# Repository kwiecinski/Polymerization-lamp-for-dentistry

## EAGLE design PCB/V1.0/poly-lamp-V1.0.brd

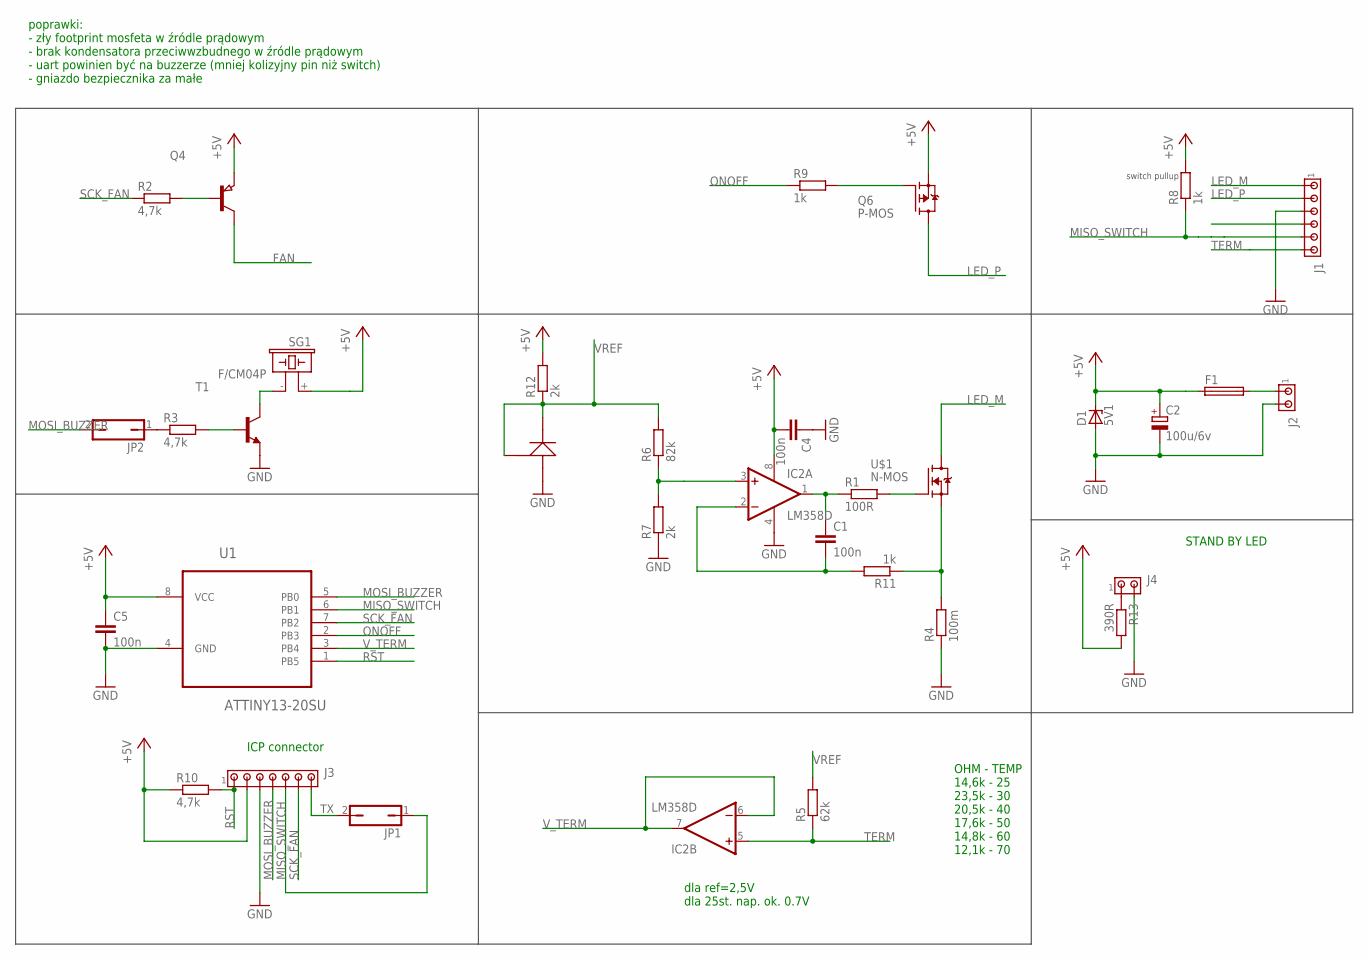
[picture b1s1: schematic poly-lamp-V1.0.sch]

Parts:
C1, C4, C5: 100n; C0805
C2: 100u/6v; E2,5-7
D1: 5V1; DO35Z10
F1: SH22,5
IC2: LM358D; SO08
J1: MTA06-100; 10X06MTA
J2, J4: MTA02-100; 10X02MTA
J3: MTA07-100; 10X07MTA
JP1, JP2: JP1Q; JP1
Q4: PNP-TRANSISTOR_SOT23; SOT23
Q6: P-MOS; TO252
R1: 100R; R0805
R2, R3, R10: 4,7k; R0805
R4: 100m; R0805
R5: 62k; R0805
R6: 82k; R0805
R7, R12: 2k; R0805
R8, R9, R11: 1k; R0805
R13: 390R; R0805
SG1: F/CM04P
T1: BC817-16-NPN-SOT23-BEC; SOT23-BEC
U1: ATTINY13-20SU; SOIC127P798X216-8N
U$1: N-MOS; TO252
U$2: TL431; SOT23-BEC

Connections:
+5V: C2.+, C4.2, C5.1, D1.C, F1.1, IC2.8 (V+), J3.2, Q4.2 (E), Q6.2 (S), R8.2, R10.1, R12.2, R13.2, SG1.+ (1), U1.8 (VCC)
FAN: J1.4, Q4.3 (C)
GND: C2.-, C4.1, C5.2, D1.A, IC2.4 (V-), J1.3, J2.2, J3.3, J4.2, R4.1, R7.1, T1.E, U1.4 (GND), U$2.C (A)
LED_M: J1.1, U$1.3 (D)
LED_P: J1.2, Q6.3 (D)
MISO_SWITCH: J1.5, J3.5, JP1.1, R8.1, U1.6 (PB1)
MOSI_BUZZER: J3.4, JP2.2, U1.5 (PB0)
unnamed: C1.1, IC2.1 (OUT), R1.1
unnamed: R1.2, U$1.1 (G)
unnamed: R3.2, T1.B
unnamed: SG1.- (2), T1.C
unnamed: Q4.1 (B), R2.2
unnamed: IC2.3 (+IN), R6.1, R7.2
unnamed: C1.2, IC2.2 (-IN), R11.2
unnamed: Q6.1 (G), R9.2
unnamed: F1.2, J2.1
unnamed: JP2.1, R3.1
unnamed: J4.1, R13.1
unnamed: R4.2, R11.1, U$1.2 (S)
ONOFF: R9.1, U1.2 (PB3)
RST: J3.1, R10.2, U1.1 (PB5)
SCK_FAN: J3.6, R2.1, U1.7 (PB2)
TERM: IC2.5 (+IN), J1.6, R5.1
TX: J3.7, JP1.2
VREF: R5.2, R6.2, R12.1, U$2.B (K), U$2.E (R)
V_TERM: IC2.6 (-IN), IC2.7 (OUT), U1.3 (PB4)

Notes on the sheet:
OHM - TEMP 14,6k - 25 23,5k - 30 20,5k - 40 17,6k - 50 14,8k - 60 12,1k - 70
dla ref=2,5V dla 25st. nap. ok. 0.7V
ICP connector
switch pullup
poprawki: - zły footprint mosfeta w źródle prądowym - brak kondensatora przeciwwzbudnego w źródle prądowym - uart powinien być na buzzerze (mniej kolizyjny pin niż switch) - gniazdo bezpiecznika za małe
STAND BY LED

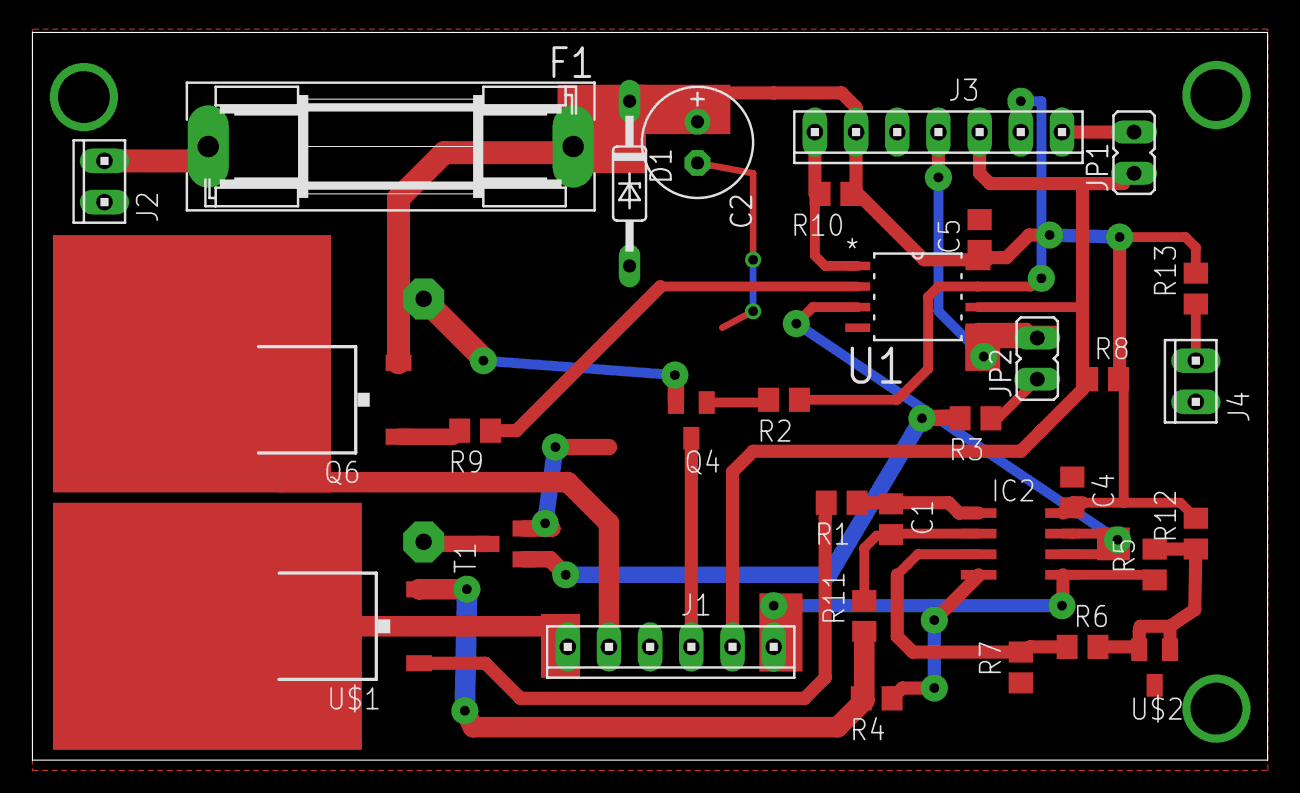
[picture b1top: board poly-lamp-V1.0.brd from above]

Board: 2 copper layers, 76.2 x 44.9 mm, 33 parts (1 on the bottom side), 26 nets.

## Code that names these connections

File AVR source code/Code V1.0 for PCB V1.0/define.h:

/*
 * define.h
 *
 *  Created on: 25 lis 2018
 *      Author: senio
 */
#define 	F_CPU   9600000UL

#define LED (1<<PB3)
#define led_off PORTB |= LED
#define led_on PORTB &= ~LED

#define BUZZ (1<<PB0)
#define buzz_on PORTB |= BUZZ
#define buzz_off PORTB &= ~BUZZ

#define FAN (1<<PB2)
#define fan_off PORTB |= FAN
#define fan_on PORTB &= ~FAN

#define SWITCH (1<<PB1)
#define SWITCH_PUSH (PINB & SWITCH)

#define true	1
#define false	0
